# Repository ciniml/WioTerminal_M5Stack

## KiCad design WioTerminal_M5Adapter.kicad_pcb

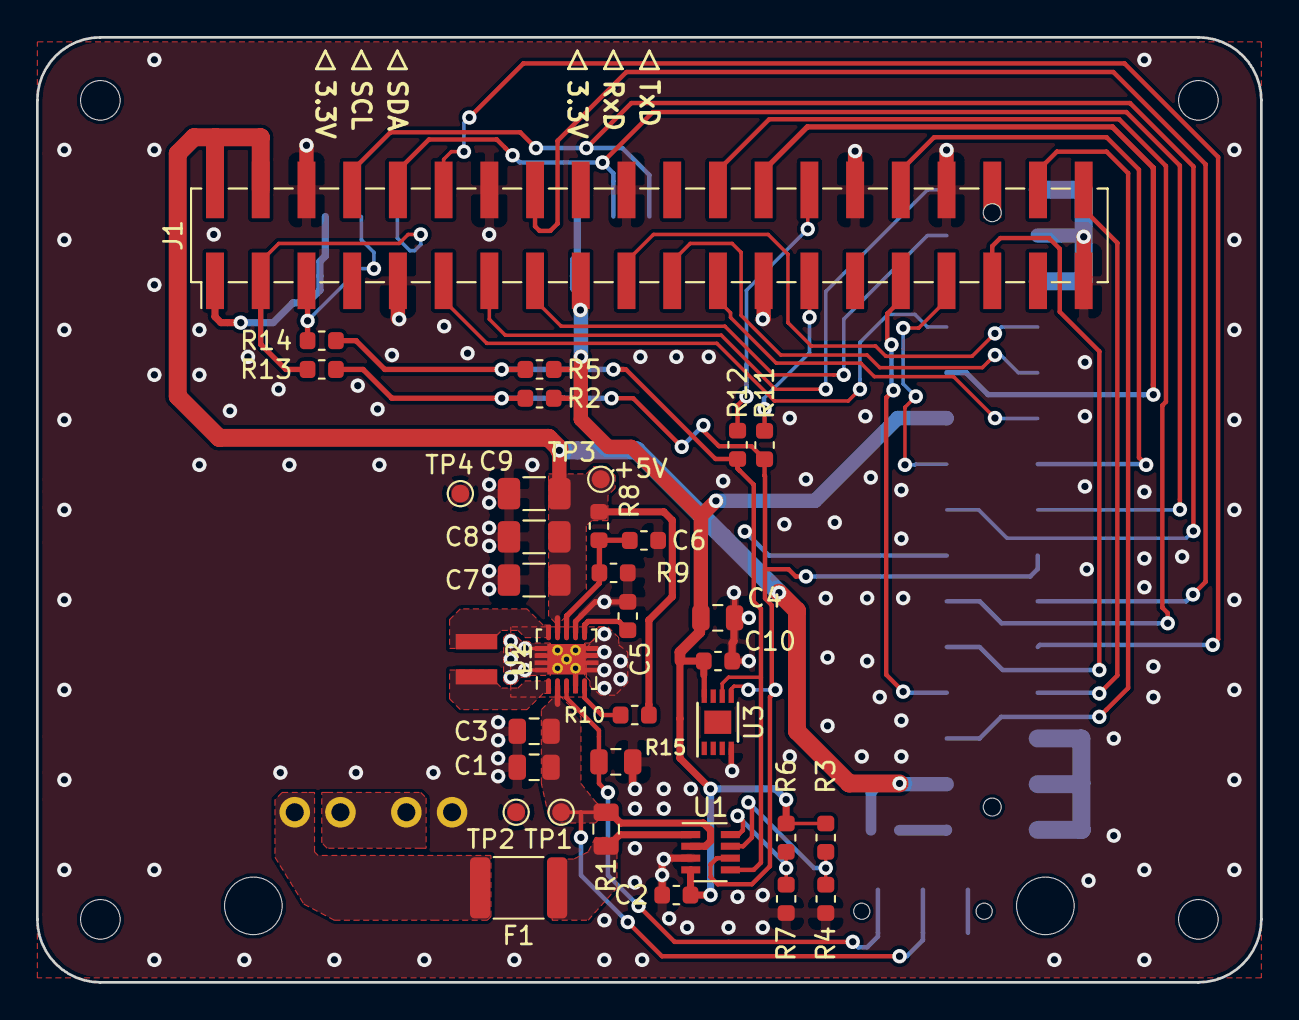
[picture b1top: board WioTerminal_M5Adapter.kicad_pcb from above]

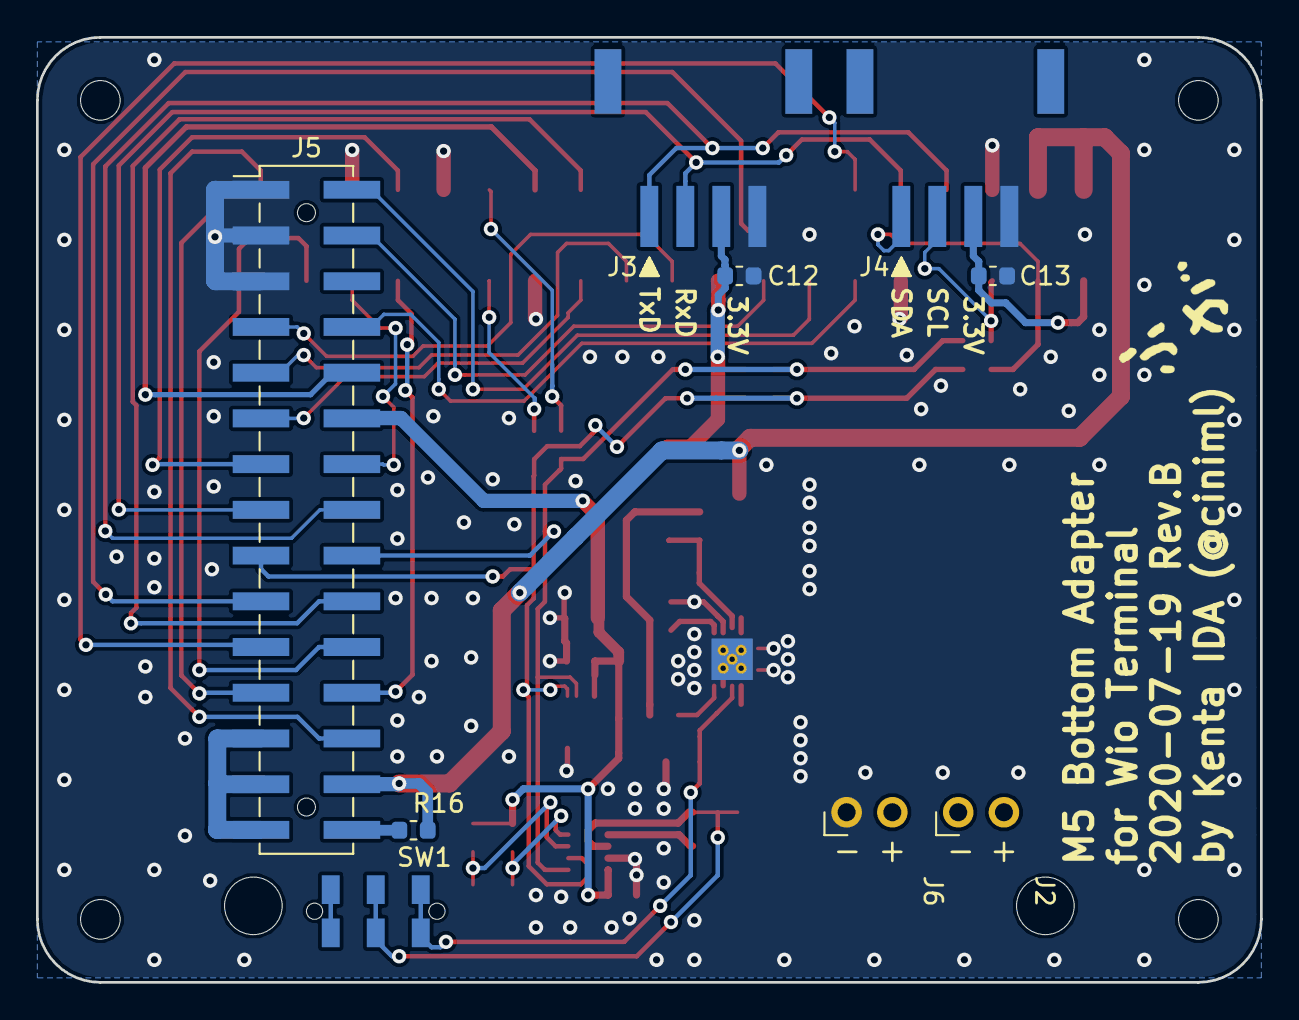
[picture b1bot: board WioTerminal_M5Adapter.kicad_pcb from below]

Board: 2 copper layers, 68.0 x 52.5 mm, 51 parts (10 on the bottom side), 41 nets.

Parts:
C1, C3, C4: 10u; C_0805_2012Metric
C2, C5, C10: 100n; C_0603_1608Metric
C6: 10p; C_0603_1608Metric
C7, C8, C9: 22u; C_1206_3216Metric
C12, C13: 1u; C_0603_1608Metric
F1: 1A; Fuse_1812_4532Metric
J1: Raspberry_Pi_2_3; PinHeader_2x20_P2.54mm_Vertical_SMD
J2, J6: Ext. BAT; PinHeader_1x02_P2.54mm_Horizontal
J3, J4: GROVE; PHS-4AW
J5: MBUS_BOTTOM; MBUS_Socket
L1: 1u, 2.5A; 74438323010
LOGO1: Logo_Open_Hardware_Small; logo
MH1, MH2, MH3, MH4: Corner; MountingHole_2.2mm_M2_DIN965
MH5, MH6: Corner; MountingHole_3.2mm_M3
R1: 0.04; R_0805_2012Metric
R2, R5: 4.7k; R_0603_1608Metric
R3, R6, R11, R12: 0; R_0603_1608Metric
R4, R7, R13, R14, R16: DNP; R_0603_1608Metric
R8, R10: 1M; R_0603_1608Metric
R9: 111k; R_0603_1608Metric
R15: 100k; R_0805_2012Metric
SW1: JS102011JAQN
TP1: BAT; TestPoint_Pad_D1.0mm
TP2: BAT-GND; TestPoint_Pad_D1.0mm
TP3: +5V; TestPoint_Pad_D1.0mm
TP4: +5V-GND; TestPoint_Pad_D1.0mm
U1: INA219AIDCN; SOT-23-8
U2: TPS63060; Texas_S-PWSON-N10_ThermalVias
U3: ATECC608A; DFN-8-1EP_3x2mm_P0.5mm_EP1.3x1.5mm

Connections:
+3V3: C2.1, C4.1, C10.1, C12.1, C13.1, J1.1, J1.17, J3.3, J4.3, J5.12, R2.1, R3.1, R5.1, R6.1, U1.4, U3.8
+5V: C7.1, C8.1, C9.1, J1.2, J1.4, J5.28, R8.1, R10.1, R16.1, TP3.1, U2.9
/A0: R3.2, R4.1, U1.7
/A0_D0: J1.13, J5.2
/A1: R6.2, R7.1, U1.8
/A1_D1: J1.15, J5.4
/A2_D2: J1.16, J5.19
/BATTERY: J5.30, R16.2
/DAC0: J1.11, J5.8
/DAC1: J1.26, J5.10
/GPCLK2: J1.31, J5.24
/HPWR: J5.25, J5.27, J5.29
/I2C1_SCL: J1.5, J4.2, R14.2
/I2C1_SDA: J1.3, J4.1, R13.2
/I2S_BCLK: J1.12, J5.21
/I2S_LRCLK: J1.35, J5.22
/I2S_SDIN: J1.38, J5.26
/I2S_SDOUT: J1.40, J5.23
/PWM0: J1.32, J5.13
/PWM1: J1.33, J5.14
/RXD: J1.10, J3.2, J5.15
/SCL: J5.18, R5.2, R12.1, R14.1, U1.5, U3.6
/SDA: J5.17, R2.2, R11.1, R13.1, U1.6, U3.5
/SPI_CS: J1.24, J5.20
/SPI_MISO: J1.21, J5.9
/SPI_MOSI: J1.19, J5.7
/SPI_SCK: J1.23, J5.11
/TXD: J1.8, J3.1, J5.16
GND: C1.2, C2.2, C3.2, C4.2, C5.2, C6.2, C7.2, C8.2, C9.2, C10.2, C12.2, C13.2, J1.6, J1.9, J1.14, J1.20, J1.25, J1.30, J1.34, J1.39, J3.4, J4.4, J5.1, J5.3, J5.5, J6.2, R4.2, R7.2, R9.2, R15.1, TP2.1, TP4.1, U1.3, U2.4, U2.7, U2.11, U3.4
unnamed: C1.1, C3.1, R1.1, SW1.2, TP1.1, U1.2, U2.2
unnamed: C5.1, U2.6
unnamed: C6.1, R8.2, R9.1, U2.8
unnamed: F1.1, R1.2, U1.1
unnamed: F1.2, J2.1
unnamed: J1.27, R11.2
unnamed: J1.28, R12.2
unnamed: J2.2, J6.1
unnamed: L1.1, U2.1
unnamed: L1.2, U2.10
unnamed: R10.2, U2.5
unnamed: R15.2, SW1.3, U2.3

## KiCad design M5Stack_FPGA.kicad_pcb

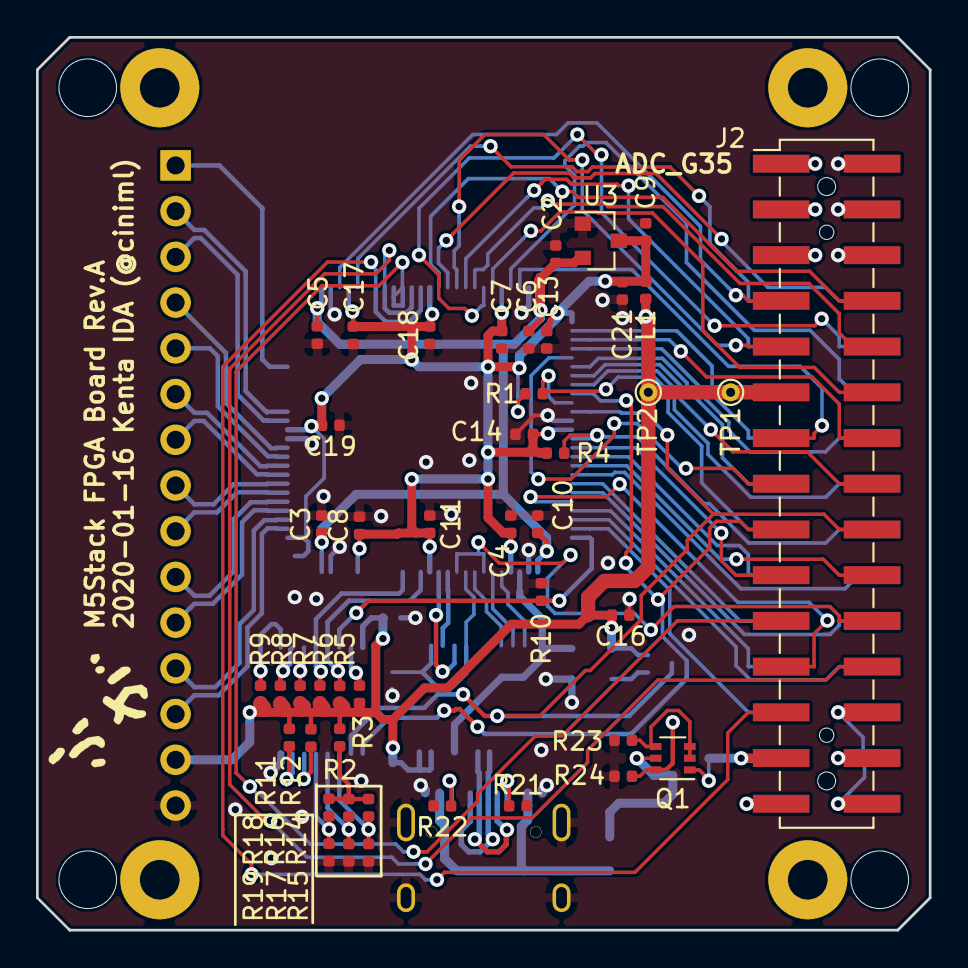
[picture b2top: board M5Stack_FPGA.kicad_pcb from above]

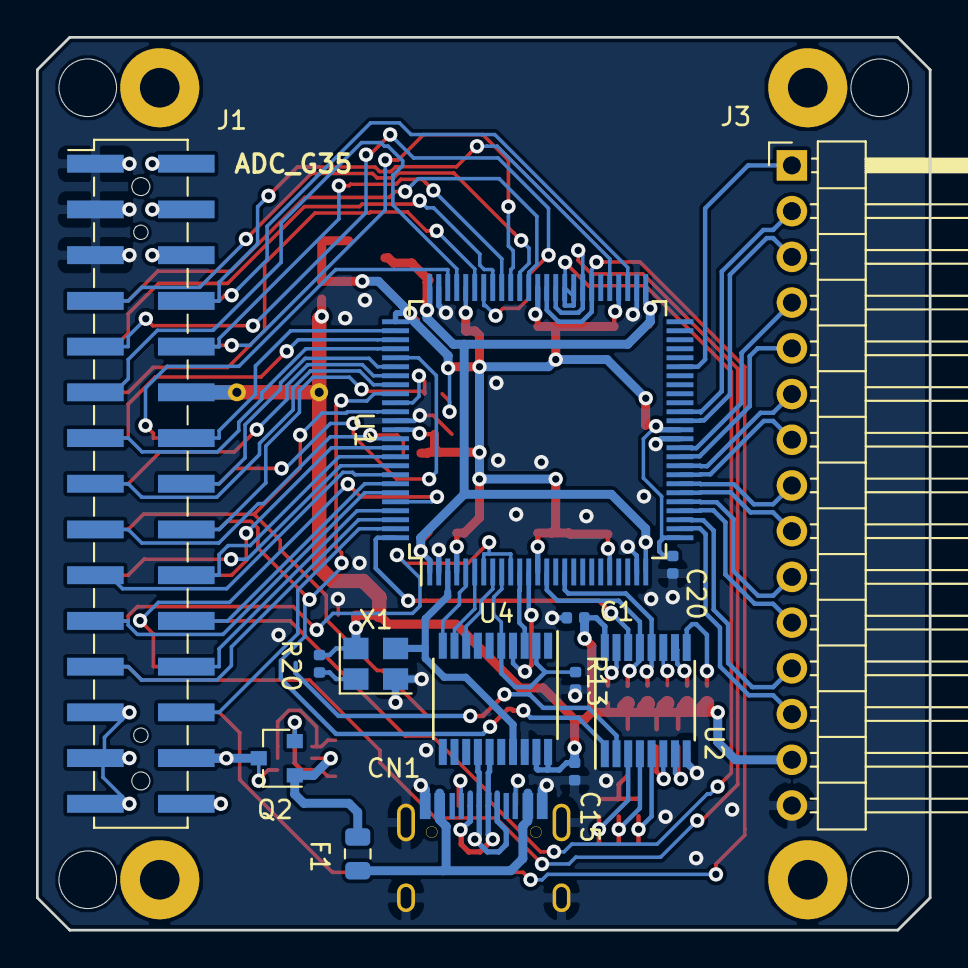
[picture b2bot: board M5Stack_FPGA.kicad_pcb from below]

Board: 2 copper layers, 49.6 x 49.6 mm, 67 parts (14 on the bottom side), 88 nets.

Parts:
C1, C3, C4, C5, C6, C7, C8, C10, C11, C13, C14, C15, C16, C17, C18, C19, C20: 100n; C_0402_1005Metric
C2, C21: 4.7u; C_0402_1005Metric
C9: 1u; C_0402_1005Metric
CN1: TYPE-C-31-M-12
F1: 1A; Fuse_0805_2012Metric
J1: MBUS_BOTTOM; MBUS_Socket
J2: MBUS_TOP; MBUS_Header
J3: Conn_01x15_Male; PinHeader_1x15_P2.54mm_Horizontal
L1: FB,600,500mA; L_0402_1005Metric
MH1, MH2, MH3, MH4: Corner; MountingHole_3.2mm_M3
MH5, MH6, MH7, MH8: Fix; MountingHole_2.2mm_M2_Pad
Q1: BCM857BS; SOT-363_SC-70-6
Q2: DMG2305UX; SOT-23
R1, R2, R3, R4: 2k; R_0402_1005Metric
R5, R10, R13: 4.7k; R_0402_1005Metric
R6, R7, R8, R9, R11, R12: 100k; R_0402_1005Metric
R14, R16, R18: NC; R_0402_1005Metric
R15, R17, R19: 0; R_0402_1005Metric
R20, R24: 47k; R_0402_1005Metric
R21, R22: 5.1k; R_0402_1005Metric
R23: 10k; R_0402_1005Metric
TP1, TP2: TestPoint; TestPoint_THTPad_D1.0mm_Drill0.5mm
U1: GW1N-4-LQ100; LQFP-100_14x14mm_P0.5mm
U2: PCA9557; TSSOP-16_4.4x5mm_P0.65mm
U3: MCP1700-1202E_SOT23; SOT-23
U4: CH552T; TSSOP-20_4.4x6.5mm_P0.65mm
X1: SG-310SCF; Crystal_SMD_3225-4Pin_3.2x2.5mm

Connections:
+1V2: C2.1, C3.1, C4.1, C5.1, C6.1, U1.1, U1.25, U1.51, U1.75, U3.2
+3V3: C1.1, C15.1, C16.2, J1.12, J2.11, J3.14, L1.1, R2.1, R3.2, R5.1, R6.1, R7.1, R8.1, R9.1, R11.1, R12.1, R20.1, TP1.1, TP2.1, U2.16, U4.19, U4.20, X1.4
+5V: J1.28, J2.27, Q1.1, Q2.3
/A0: R14.2, R15.1, U2.3
/A1: R16.2, R17.1, U2.4
/A2: R18.2, R19.1, U2.5
/ADC_G35: J1.2, J2.1
/ADC_G36: J1.4, J2.3
/BATTERY: J1.30, J2.29
/CC1: CN1.A5, R21.1
/CC2: CN1.B5, R22.1
/DAC: J2.9, U1.66
/DAC_SPK: J2.7, U1.53
/FPGA_3V3: C7.1, C8.1, C9.1, C10.2, C11.2, C13.2, C14.2, C17.2, C18.2, C19.2, C20.2, C21.1, L1.2, R1.1, R4.1, U1.4, U1.13, U1.21, U1.26, U1.38, U1.54, U1.63, U1.71, U1.76, U1.88, U3.3
/F_DAC: J1.10, U1.67
/F_DAC_SPK: J1.8, U1.55
/F_GPIO_G2: J1.19, U1.93
/F_GPIO_G5: J1.20, U1.91
/F_IIS_IN: J1.26, U1.99
/F_IIS_MK: J1.24, U1.97
/F_IIS_OUT: J1.23, U1.98
/F_IIS_SK: J1.21, U1.95
/F_IIS_WS: J1.22, U1.94
/F_MISO: J1.9, U1.69
/F_MOSI: J1.7, U1.65
/F_RXD0: J1.13, U1.79
/F_RXD2: J1.15, U1.83
/F_SCK: J1.11, U1.72
/F_SCL: J1.18, R1.2, U1.85
/F_SDA: J1.17, R4.2, U1.89
/F_TXD0: J1.14, U1.77
/F_TXD2: J1.16, U1.81
/GPIO_G2: J2.20, U1.92
/GPIO_G5: J2.19, U1.90
/HPWR: J1.25, J1.27, J1.29, J2.26, J2.28, J2.30
/IIS_MK: J2.23, U1.96
/IOB6_N: J3.12, U1.28
/IOB6_P: J3.13, U1.27
/IOB8_N: J3.10, U1.30
/IOB8_P: J3.11, U1.29
/IOB10_N: J3.8, U1.32
/IOB10_P: J3.9, U1.31
/IOB12_N: J3.6, U1.34
/IOB12_P: J3.7, U1.33
/IOB14_N: J3.4, U1.36
/IOB14_P: J3.5, U1.35
/IOB19_N: J3.2, U1.40
/IOB19_P: J3.3, U1.39
/IOB26A: J3.1, U1.45
/JTAG_TCK: R13.1, U1.9, U4.2, U4.5
/JTAG_TDI: U1.11, U4.3
/JTAG_TDO: U1.12, U4.4
/JTAG_TMS: U1.8, U4.8
/MISO: J2.10, U1.68
/MODE0: R10.1, U1.100, U2.14
/MOSI: J2.8, U1.64
/OSC_24M: U1.3, U4.17, X1.3
/OSC_24M_OE: R20.2, X1.1
/PROG_RX0: U1.5, U4.10
/PROG_TX0: U1.6, U4.9
/READY: R6.2, U1.16, U2.12
/RECONFIG_N: R5.2, U1.14, U2.13
/RST: J1.6, J2.5
/RXD0: J2.14, U1.78
/RXD2: J2.16, U1.82
/SCK: J2.12, U1.70
/SCL: J2.17, U1.84, U2.1
/SDA: J2.18, U1.86, U2.2
/SSPI_CS_N_IIS_WS: J2.21, U1.59, U1.60
/SSPI_SCLK_IIS_SK: J2.22, U1.7, U1.10
/SSPI_SI_IIS_IN: J2.25, U1.57, U1.62
/SSPI_SO_IIS_OUT: J2.24, U1.58, U1.61
/TXD0: J2.13, U1.73
/TXD2: J2.15, U1.80
/USB_D+: CN1.A6, CN1.B6, U4.14
/USB_D-: CN1.A7, CN1.B7, U4.15
/VBUS: CN1.A4, CN1.A9, F1.2
GND: C1.2, C2.2, C3.2, C4.2, C5.2, C6.2, C7.2, C8.2, C9.2, C10.1, C11.1, C13.1, C14.1, C15.2, C16.1, C17.1, C18.1, C19.1, C20.1, C21.2, CN1.A1, CN1.A12, CN1.PAD, J1.1, J1.3, J1.5, J2.2, J2.4, J2.6, J3.15, R10.2, R13.2, R15.2, R17.2, R19.2, R21.2, R22.2, R23.2, R24.2, U1.2, U1.24, U1.37, U1.52, U1.74, U1.87, U2.8, U3.1, U4.18, X1.2
unnamed: F1.1, Q1.5, Q2.1
unnamed: Q1.2, Q1.3, Q1.4, R23.1
unnamed: Q1.6, Q2.2, R24.1
unnamed: R3.1, U2.15
unnamed: R7.2, U2.11
unnamed: R8.2, U2.10
unnamed: R9.2, U2.9
unnamed: R11.2, U2.7
unnamed: R12.2, U2.6
unnamed: R2.2, R14.1, R16.1, R18.1

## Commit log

2020-01-14 End circuit design
2020-01-15 Partially routed
2020-01-15 Routed vital nets
2020-02-08 Revision A Add Enclosure
2020-06-14 Revision A
2020-07-12 Add Enclosure
2020-07-20 Fix INA-219 pin assignment
2020-07-20 Add NMT jumper between MBUS +5V and BAT.
